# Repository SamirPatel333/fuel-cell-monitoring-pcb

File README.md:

# Fuel Cell Monitoring System – 6-Layer PCB

## Overview

A custom **6-layer mixed-signal PCB** designed in **KiCad** for monitoring a **PEM fuel cell system**.

The board measures fuel-cell voltage and current, conditions the analog signals, performs ADC conversion, provides digital isolation, and interfaces with an **ESP32-S3**.

## Main Features

- Fuel-cell voltage measurement
- Fuel-cell current measurement up to 20 A
- Analog signal conditioning and filtering
- Precision voltage references
- High-resolution ADC measurement
- Digital isolation
- ESP32-S3 interface

## Main Components

| Component | Function |
|---|---|
| ESP32-S3 | Microcontroller |
| ADS8329 | ADC |
| MAX49925 | Current measurement |
| MAX6070 | Precision voltage reference |
| AD8031 / AD8032 | Analog signal conditioning |
| ADA4099 | Precision analog amplifier |

## PCB Design

The PCB is designed as a **6-layer mixed-signal board** using KiCad.

The multilayer design supports:

- Analog and digital signal separation
- Stable power and ground distribution
- Sensitive ADC signal routing
- High-current routing
- Improved signal integrity and noise performance

## Design Tools

- KiCad – Schematic capture and PCB layout
- ESP32-S3 – Microcontroller interface
- Multilayer PCB design for mixed-signal applications

## Project Structure

- `Kicad/` – KiCad schematics, PCB layout, symbols and footprints
- `Docs/` – Project report and documentation images
- `.gitignore` – Files excluded from Git tracking

## Project Status

PCB schematic and 6-layer PCB layout completed in KiCad.

## Future Improvements

- PCB manufacturing and assembly
- Hardware testing and calibration
- ESP32-S3 firmware development
- Measurement accuracy and noise evaluation

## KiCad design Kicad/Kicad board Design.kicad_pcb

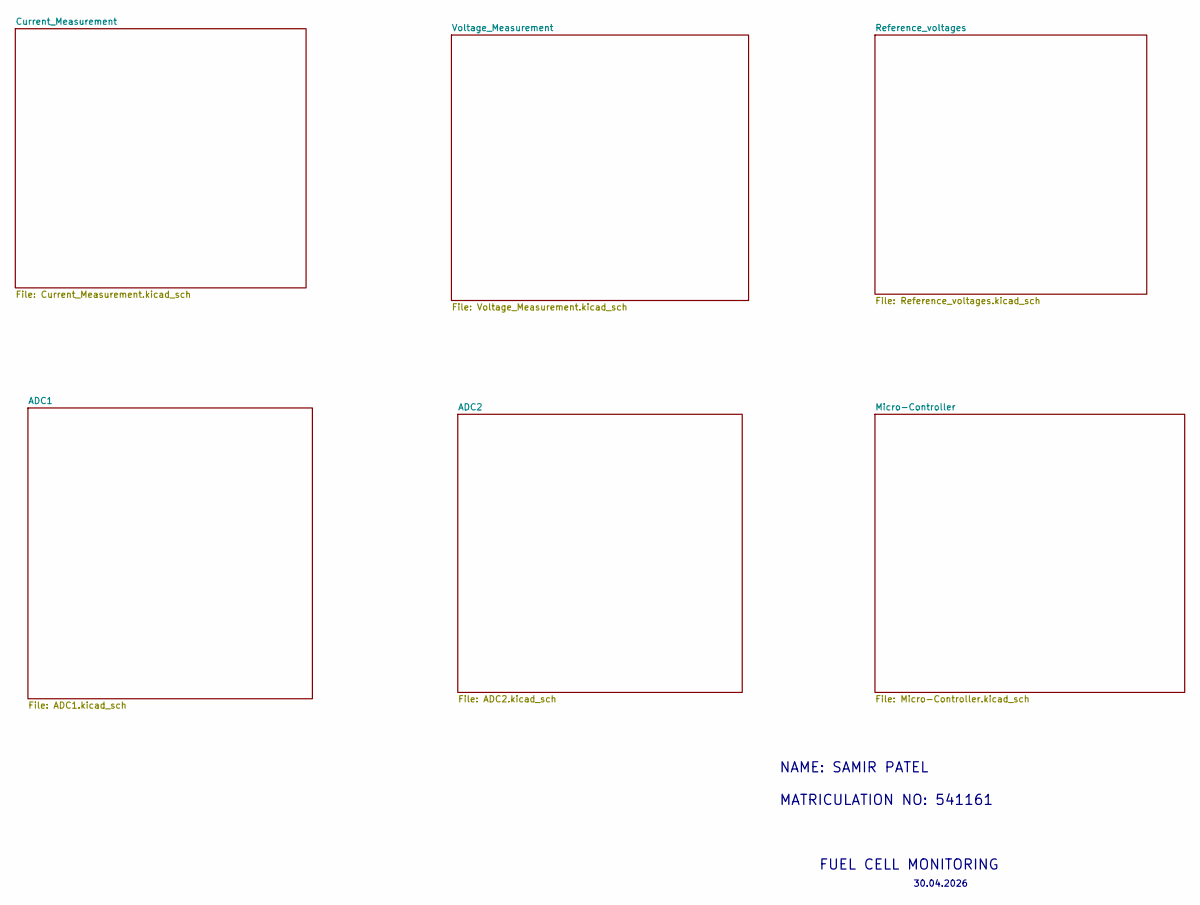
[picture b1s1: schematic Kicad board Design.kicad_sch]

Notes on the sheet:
FUEL CELL MONITORING
30.04.2026
NAME: SAMIR PATEL MATRICULATION NO: 541161

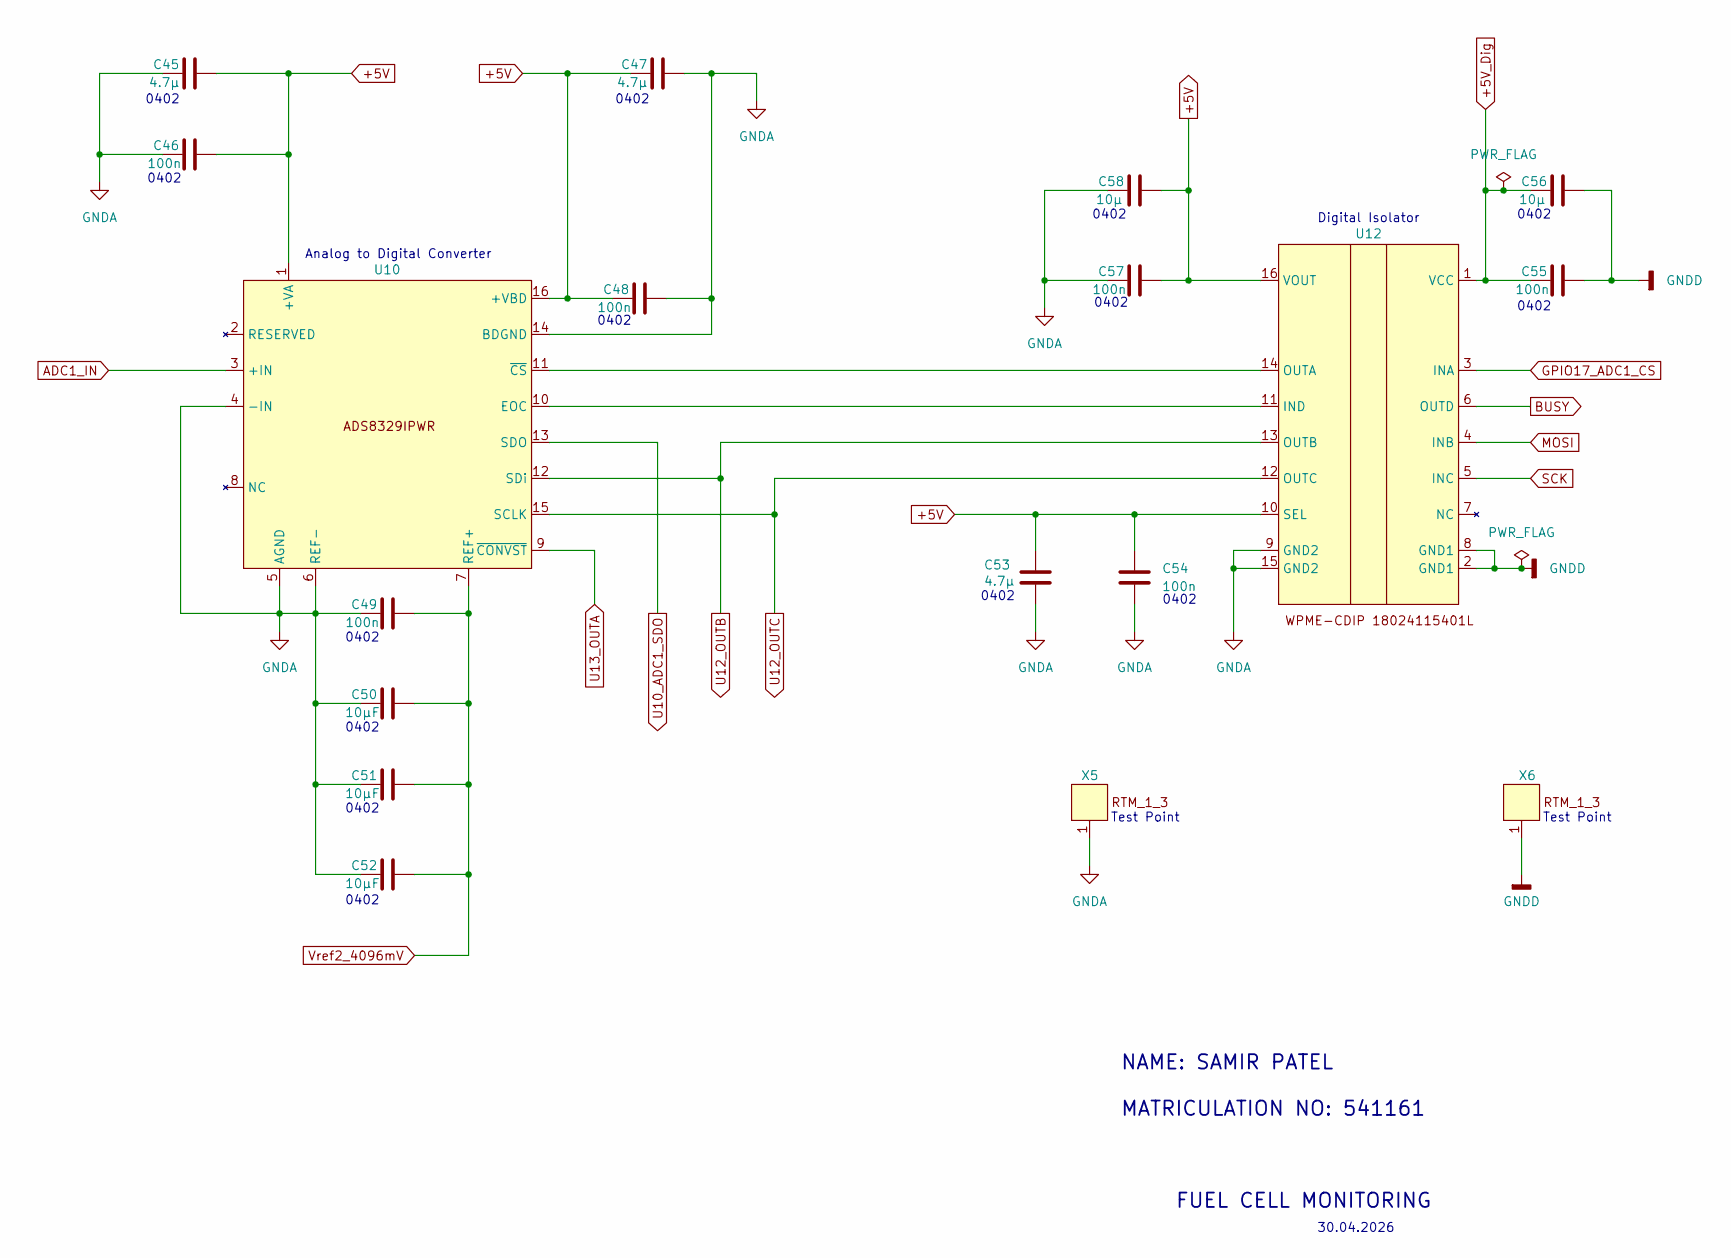
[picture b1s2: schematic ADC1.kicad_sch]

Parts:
C45, C47, C53: 4.7µ; C_0402_1005Metric
C46, C48, C49, C54, C55, C57: 100n; C_0402_1005Metric
C50, C51, C52: 10µF; C_0402_1005Metric
C56, C58: 10µ; C_0402_1005Metric
U10: ADS8329IPWR
U12: WPME-CDIP 18024115401L
X5, X6: RTM_1_3

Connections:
+5V: C45.2, C46.2, C47.1, C48.1, C53.1, C54.1, C57.2, C58.2, U10.1 (+VA), U10.16 (+VBD), U12.10 (SEL), U12.16 (VOUT); also elsewhere on the board
+5V_Dig: C55.1, C56.1, U12.1 (VCC); also elsewhere on the board
ADC1_IN: U10.3 (+IN); also elsewhere on the board
BUSY: U12.6 (OUTD); also elsewhere on the board
GNDA: C45.1, C46.1, C47.2, C48.2, C49.1, C50.1, C51.1, C52.1, C53.2, C54.2, C57.1, C58.1, U10.4 (-IN), U10.5 (AGND), U10.6 (REF-), U10.14 (BDGND), U12.9 (GND2), U12.15 (GND2), X5.1; also elsewhere on the board
GNDD: C55.2, C56.2, U12.2 (GND1), U12.8 (GND1), X6.1; also elsewhere on the board
GPIO17_ADC1_CS: U12.3 (INA); also elsewhere on the board
MOSI: U12.4 (INB); also elsewhere on the board
unnamed: U10.10 (EOC), U12.11 (IND)
unnamed: U10.11 (~CS), U12.14 (OUTA)
SCK: U12.5 (INC); also elsewhere on the board
U10_ADC1_SDO: U10.13 (SDO); also elsewhere on the board
U12_OUTB: U10.12 (SDi), U12.13 (OUTB); also elsewhere on the board
U12_OUTC: U10.15 (SCLK), U12.12 (OUTC); also elsewhere on the board
U13_OUTA: U10.9 (~CONVST); also elsewhere on the board
Vref2_4096mV: C49.2, C50.2, C51.2, C52.2, U10.7 (REF+); also elsewhere on the board

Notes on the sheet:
0402
Test Point
Analog to Digital Converter
NAME: SAMIR PATEL MATRICULATION NO: 541161
30.04.2026
Digital Isolator
FUEL CELL MONITORING

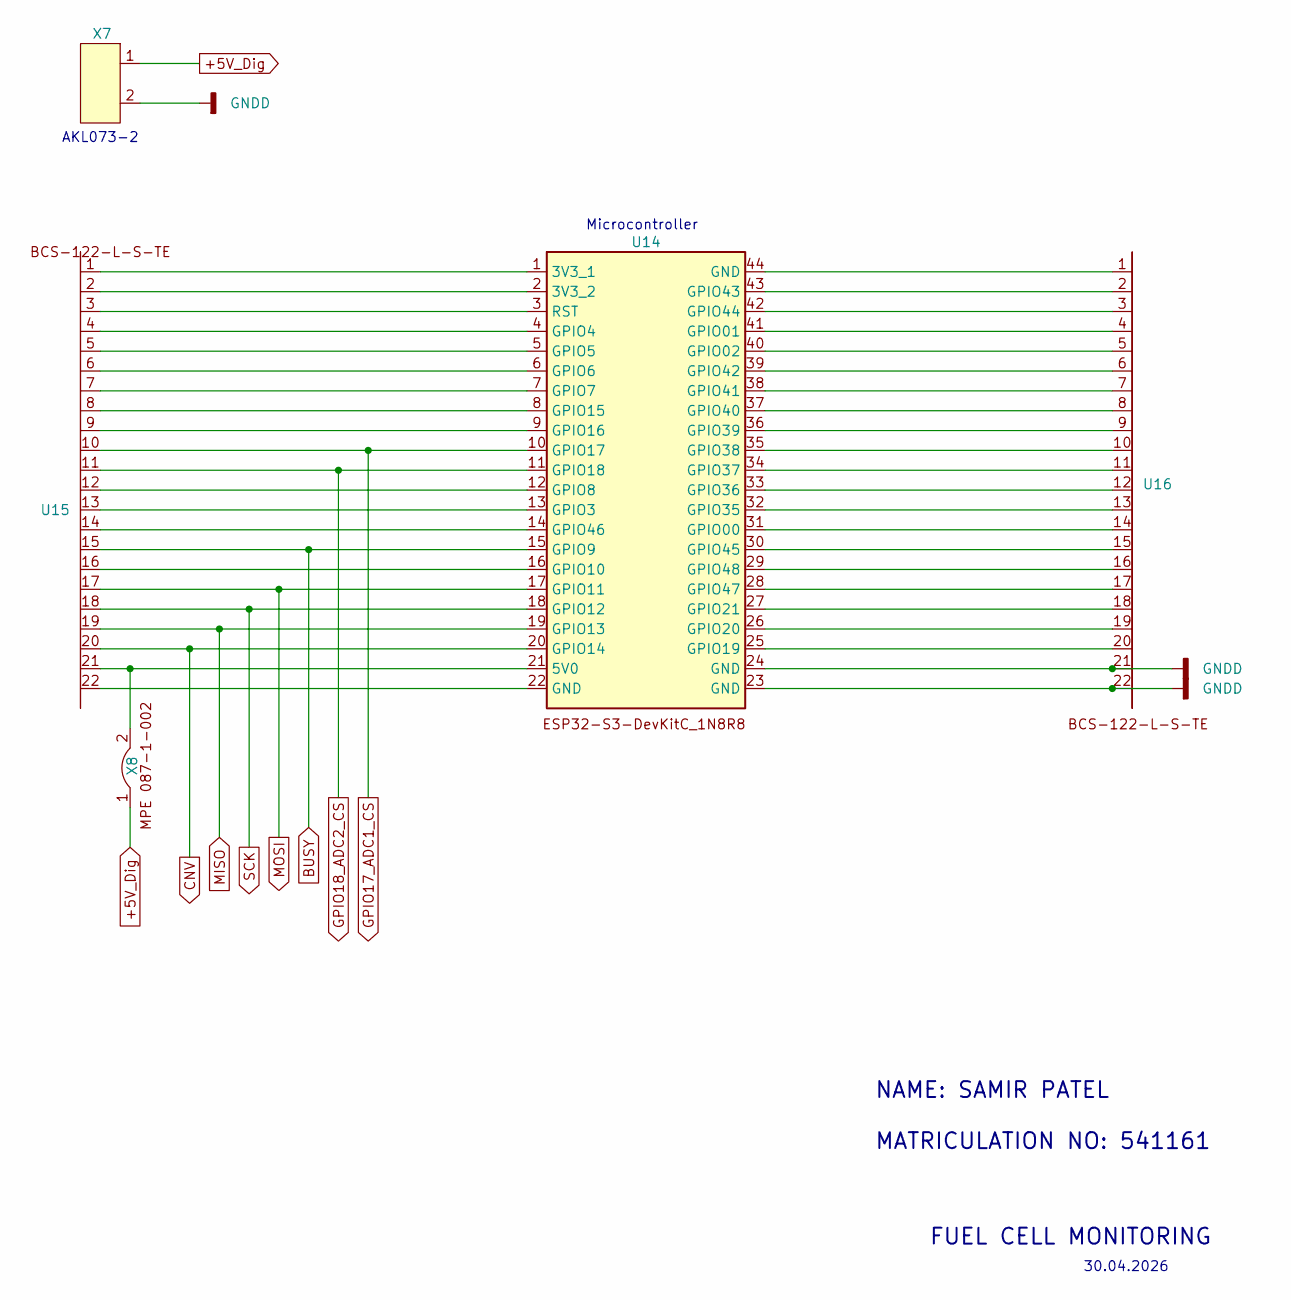
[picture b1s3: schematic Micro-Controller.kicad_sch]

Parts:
U14: ESP32-S3-DevkitC-1N8R8
U15, U16: BCS-122-L-S-TE
X7: AKL073-2
X8: MPE_087

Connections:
+5V_Dig: X7.1, X8.1; also elsewhere on the board
BUSY: U14.15 (GPIO9), U15.15; also elsewhere on the board
CNV: U14.20 (GPIO14), U15.20; also elsewhere on the board
GNDD: U14.23 (GND), U14.24 (GND), U16.21, U16.22, X7.2; also elsewhere on the board
GPIO17_ADC1_CS: U14.10 (GPIO17), U15.10; also elsewhere on the board
GPIO18_ADC2_CS: U14.11 (GPIO18), U15.11; also elsewhere on the board
MISO: U14.19 (GPIO13), U15.19; also elsewhere on the board
MOSI: U14.17 (GPIO11), U15.17; also elsewhere on the board
unnamed: U14.1 (3V3_1), U15.1
unnamed: U14.2 (3V3_2), U15.2
unnamed: U14.3 (RST), U15.3
unnamed: U14.4 (GPIO4), U15.4
unnamed: U14.5 (GPIO5), U15.5
unnamed: U14.6 (GPIO6), U15.6
unnamed: U14.7 (GPIO7), U15.7
unnamed: U14.8 (GPIO15), U15.8
unnamed: U14.9 (GPIO16), U15.9
unnamed: U14.12 (GPIO8), U15.12
unnamed: U14.13 (GPIO3), U15.13
unnamed: U14.14 (GPIO46), U15.14
unnamed: U14.16 (GPIO10), U15.16
unnamed: U14.21 (5V0), U15.21, X8.2
unnamed: U14.22 (GND), U15.22
unnamed: U14.44 (GND), U16.1
unnamed: U14.43 (GPIO43), U16.2
unnamed: U14.42 (GPIO44), U16.3
unnamed: U14.41 (GPIO01), U16.4
unnamed: U14.40 (GPIO02), U16.5
unnamed: U14.39 (GPIO42), U16.6
unnamed: U14.38 (GPIO41), U16.7
unnamed: U14.37 (GPIO40), U16.8
unnamed: U14.36 (GPIO39), U16.9
unnamed: U14.35 (GPIO38), U16.10
unnamed: U14.34 (GPIO37), U16.11
unnamed: U14.33 (GPIO36), U16.12
unnamed: U14.32 (GPIO35), U16.13
unnamed: U14.31 (GPIO00), U16.14
unnamed: U14.30 (GPIO45), U16.15
unnamed: U14.29 (GPIO48), U16.16
unnamed: U14.28 (GPIO47), U16.17
unnamed: U14.27 (GPIO21), U16.18
unnamed: U14.26 (GPIO20), U16.19
unnamed: U14.25 (GPIO19), U16.20
SCK: U14.18 (GPIO12), U15.18; also elsewhere on the board

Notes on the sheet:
30.04.2026
Microcontroller
NAME: SAMIR PATEL MATRICULATION NO: 541161
FUEL CELL MONITORING
AKL073-2

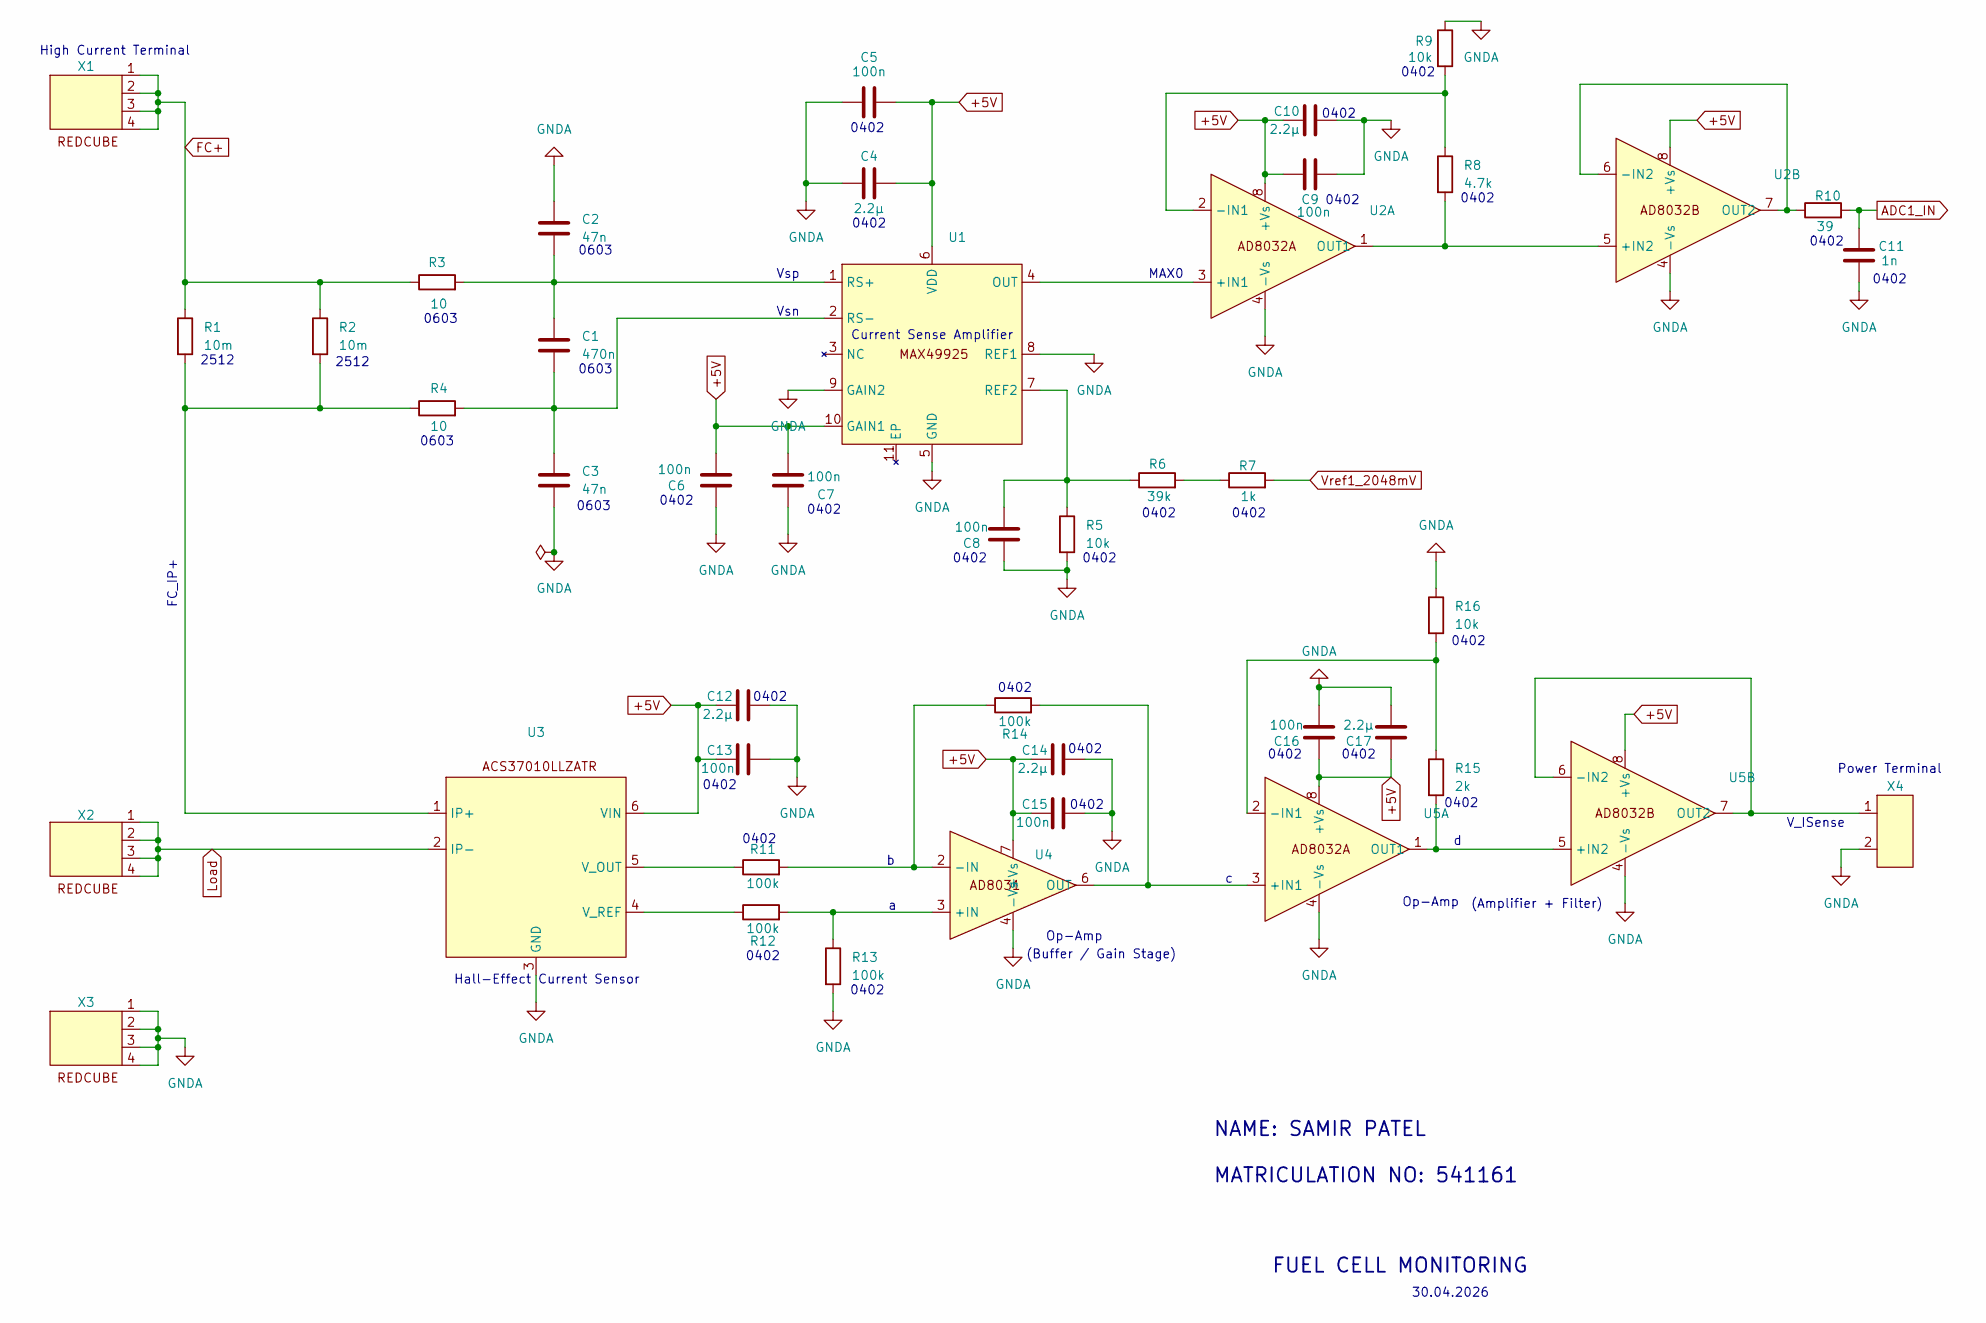
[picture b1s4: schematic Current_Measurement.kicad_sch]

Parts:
C1: 470n; C_0603_1608Metric
C2, C3: 47n; C_0603_1608Metric
C4, C10, C12, C14, C17: 2.2µ; C_0402_1005Metric
C5, C6, C7, C8, C9, C13, C15, C16: 100n; C_0402_1005Metric
C11: 1n; C_0402_1005Metric
R1, R2: 10m; R_2512_6332Metric
R3, R4: 10; R_0603_1608Metric
R5, R9, R16: 10k; R_0402_1005Metric
R6: 39k; R_0402_1005Metric
R7: 1k; R_0402_1005Metric
R8: 4.7k; R_0402_1005Metric
R10: 39; R_0402_1005Metric
R11, R12, R13, R14: 100k; R_0402_1005Metric
R15: 2k; R_0402_1005Metric
U1: MAX49925XATB+T
U2, U5: AD8032ARZ
U3: ACS37010LLZATR-030U5
U4: AD8031ARZ
X1, X2, X3: WP-THRBU_REDCUBE_74650073
X4: AKL073-2

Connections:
+5V: C4.2, C5.2, C6.1, C7.1, C9.1, C10.1, C12.1, C13.1, C14.1, C15.1, C16.2, C17.2, U1.6 (VDD), U1.10 (GAIN1), U2.8 (+Vs), U3.6 (VIN), U4.7 (+Vs), U5.8 (+Vs); also elsewhere on the board
ADC1_IN: C11.1, R10.2; also elsewhere on the board
FC+: R1.1, R2.1, R3.1, X1.1, X1.2, X1.3, X1.4; also elsewhere on the board
GNDA: C2.1, C3.2, C4.1, C5.1, C6.2, C7.2, C8.2, C9.2, C10.2, C11.2, C12.2, C13.2, C14.2, C15.2, C16.1, C17.1, R5.2, R9.1, R13.2, R16.1, U1.5 (GND), U1.8 (REF1), U1.9 (GAIN2), U2.4 (-Vs), U3.3 (GND), U4.4 (-Vs), U5.4 (-Vs), X3.1, X3.2, X3.3, X3.4, X4.2; also elsewhere on the board
Load: U3.2 (IP-), X2.1, X2.2, X2.3, X2.4
unnamed: R6.2, R7.1
unnamed: U1.4 (OUT), U2.3 (+IN1)
unnamed: C8.1, R5.1, R6.1, U1.7 (REF2)
unnamed: C1.1, C2.2, R3.2, U1.1 (RS+)
unnamed: C1.2, C3.1, R4.2, U1.2 (RS-)
unnamed: R8.1, R9.2, U2.2 (-IN1)
unnamed: R8.2, U2.1 (OUT1), U2.5 (+IN2)
unnamed: R10.1, U2.6 (-IN2), U2.7 (OUT2)
unnamed: R1.2, R2.2, R4.1, U3.1 (IP+)
unnamed: R11.1, U3.5 (V_OUT)
unnamed: R12.1, U3.4 (V_REF)
unnamed: R12.2, R13.1, U4.3 (+IN)
unnamed: R11.2, R14.1, U4.2 (-IN)
unnamed: R14.2, U4.6 (OUT), U5.3 (+IN1)
unnamed: R15.1, R16.2, U5.2 (-IN1)
unnamed: R15.2, U5.1 (OUT1), U5.5 (+IN2)
unnamed: U5.6 (-IN2), U5.7 (OUT2), X4.1
Vref1_2048mV: R7.2; also elsewhere on the board

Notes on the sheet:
Hall-Effect Current Sensor
0402
2512
0603
V_ISense
FUEL CELL MONITORING
Vsp
Current Sense Amplifier
NAME: SAMIR PATEL MATRICULATION NO: 541161
High Current Terminal
Vsn
30.04.2026
(Buffer / Gain Stage)
FC_IP+
Op-Amp
MAX0
(Amplifier + Filter)
Power Terminal

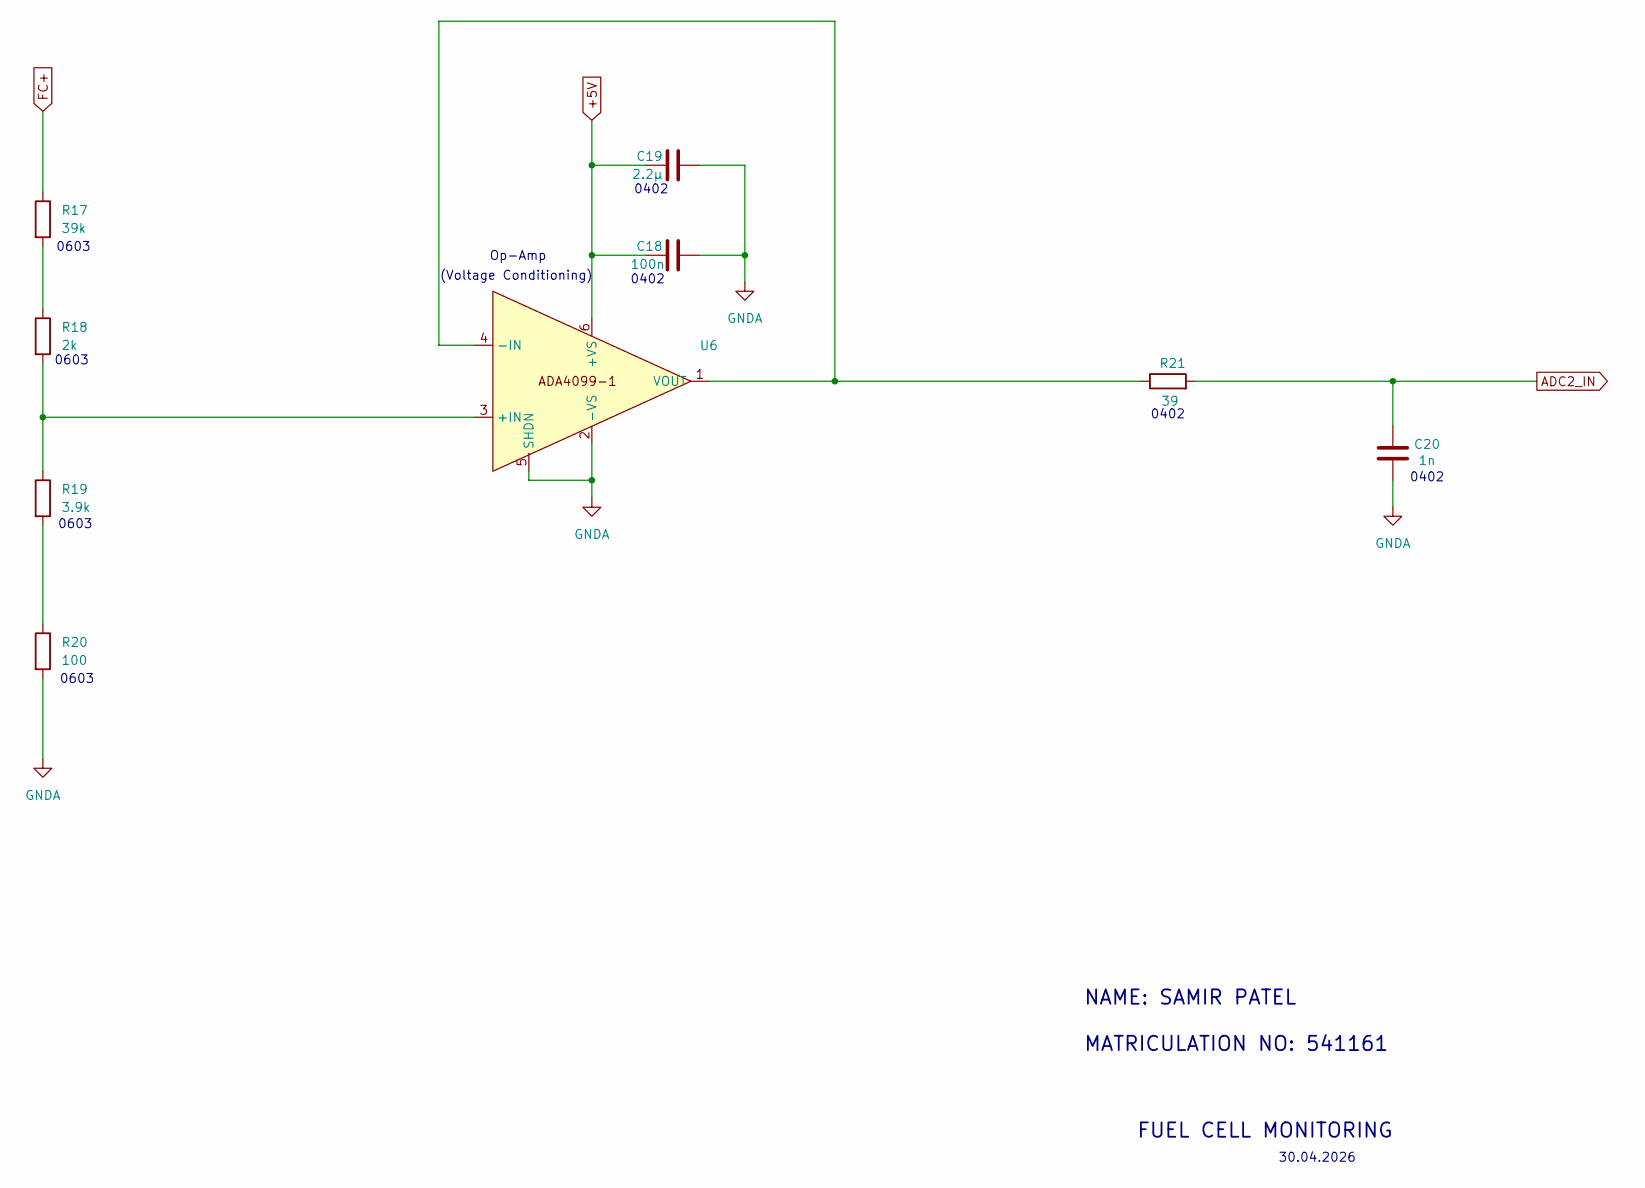
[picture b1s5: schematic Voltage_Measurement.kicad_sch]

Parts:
C18: 100n; C_0402_1005Metric
C19: 2.2µ; C_0402_1005Metric
C20: 1n; C_0402_1005Metric
R17: 39k; R_0603_1608Metric
R18: 2k; R_0603_1608Metric
R19: 3.9k; R_0603_1608Metric
R20: 100; R_0603_1608Metric
R21: 39; R_0402_1005Metric
U6: ADA4099-1BUJZ-RL7

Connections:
+5V: C18.1, C19.1, U6.6 (+VS); also elsewhere on the board
ADC2_IN: C20.1, R21.2; also elsewhere on the board
FC+: R17.1; also elsewhere on the board
GNDA: C18.2, C19.2, C20.2, R20.2, U6.2 (-VS), U6.5 (SHDN); also elsewhere on the board
unnamed: R17.2, R18.1
unnamed: R19.2, R20.1
unnamed: R18.2, R19.1, U6.3 (+IN)
unnamed: R21.1, U6.1 (VOUT), U6.4 (-IN)

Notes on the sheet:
0402
0603
(Voltage Conditioning)
FUEL CELL MONITORING
Op-Amp
NAME: SAMIR PATEL MATRICULATION NO: 541161
30.04.2026

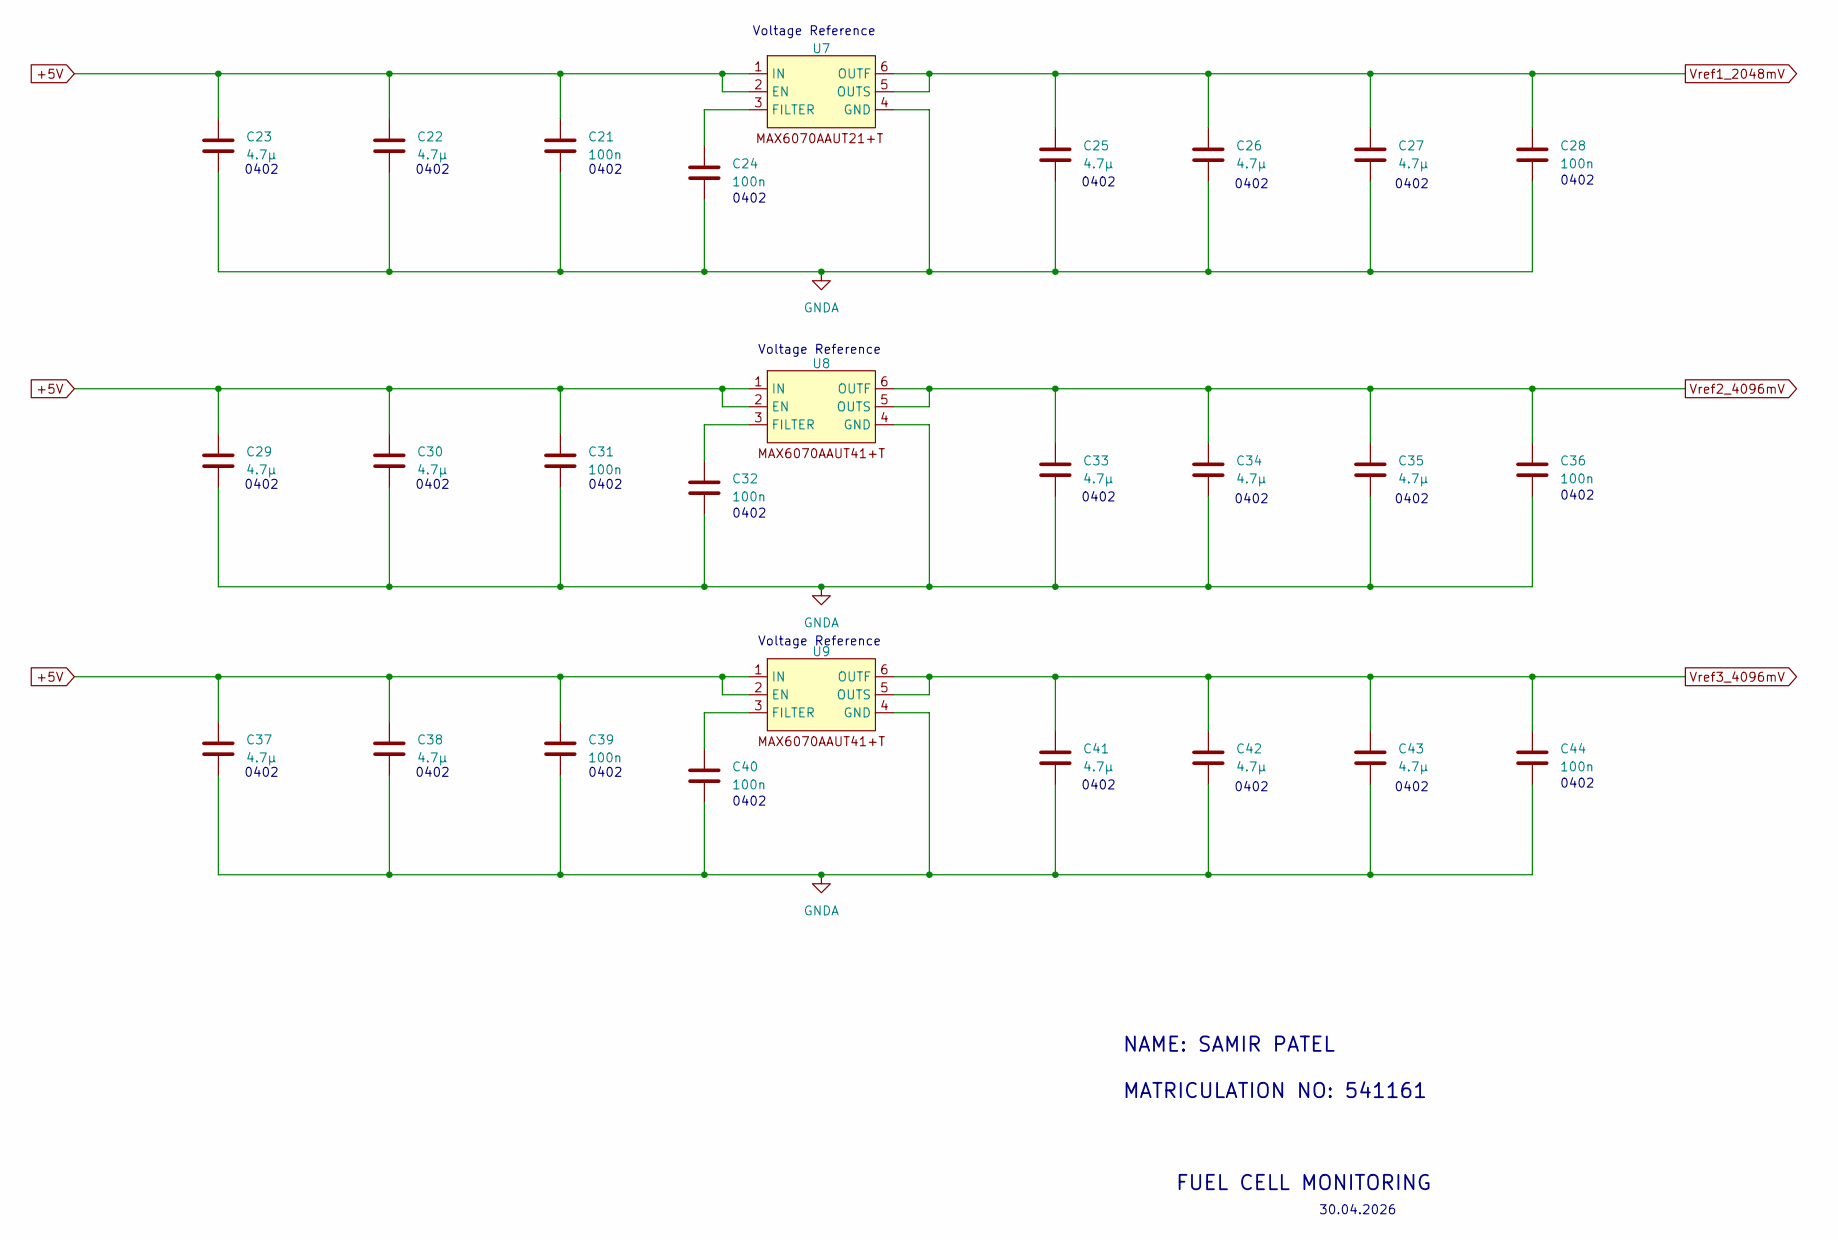
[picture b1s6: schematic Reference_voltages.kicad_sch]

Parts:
C21, C24, C28, C31, C32, C36, C39, C40, C44: 100n; C_0402_1005Metric
C22, C23, C25, C26, C27, C29, C30, C33, C34, C35, C37, C38, C41, C42, C43: 4.7µ; C_0402_1005Metric
U7: MAX6070AAUT21+T
U8, U9: MAX6070AAUT41+T

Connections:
+5V: C21.1, C22.1, C23.1, C29.1, C30.1, C31.1, C37.1, C38.1, C39.1, U7.1 (IN), U7.2 (EN), U8.1 (IN), U8.2 (EN), U9.1 (IN), U9.2 (EN); also elsewhere on the board
GNDA: C21.2, C22.2, C23.2, C24.2, C25.2, C26.2, C27.2, C28.2, C29.2, C30.2, C31.2, C32.2, C33.2, C34.2, C35.2, C36.2, C37.2, C38.2, C39.2, C40.2, C41.2, C42.2, C43.2, C44.2, U7.4 (GND), U8.4 (GND), U9.4 (GND); also elsewhere on the board
unnamed: C24.1, U7.3 (FILTER)
unnamed: C32.1, U8.3 (FILTER)
unnamed: C40.1, U9.3 (FILTER)
Vref1_2048mV: C25.1, C26.1, C27.1, C28.1, U7.5 (OUTS), U7.6 (OUTF); also elsewhere on the board
Vref2_4096mV: C33.1, C34.1, C35.1, C36.1, U8.5 (OUTS), U8.6 (OUTF); also elsewhere on the board
Vref3_4096mV: C41.1, C42.1, C43.1, C44.1, U9.5 (OUTS), U9.6 (OUTF); also elsewhere on the board

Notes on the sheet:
Voltage Reference
0402
30.04.2026
FUEL CELL MONITORING
NAME: SAMIR PATEL MATRICULATION NO: 541161

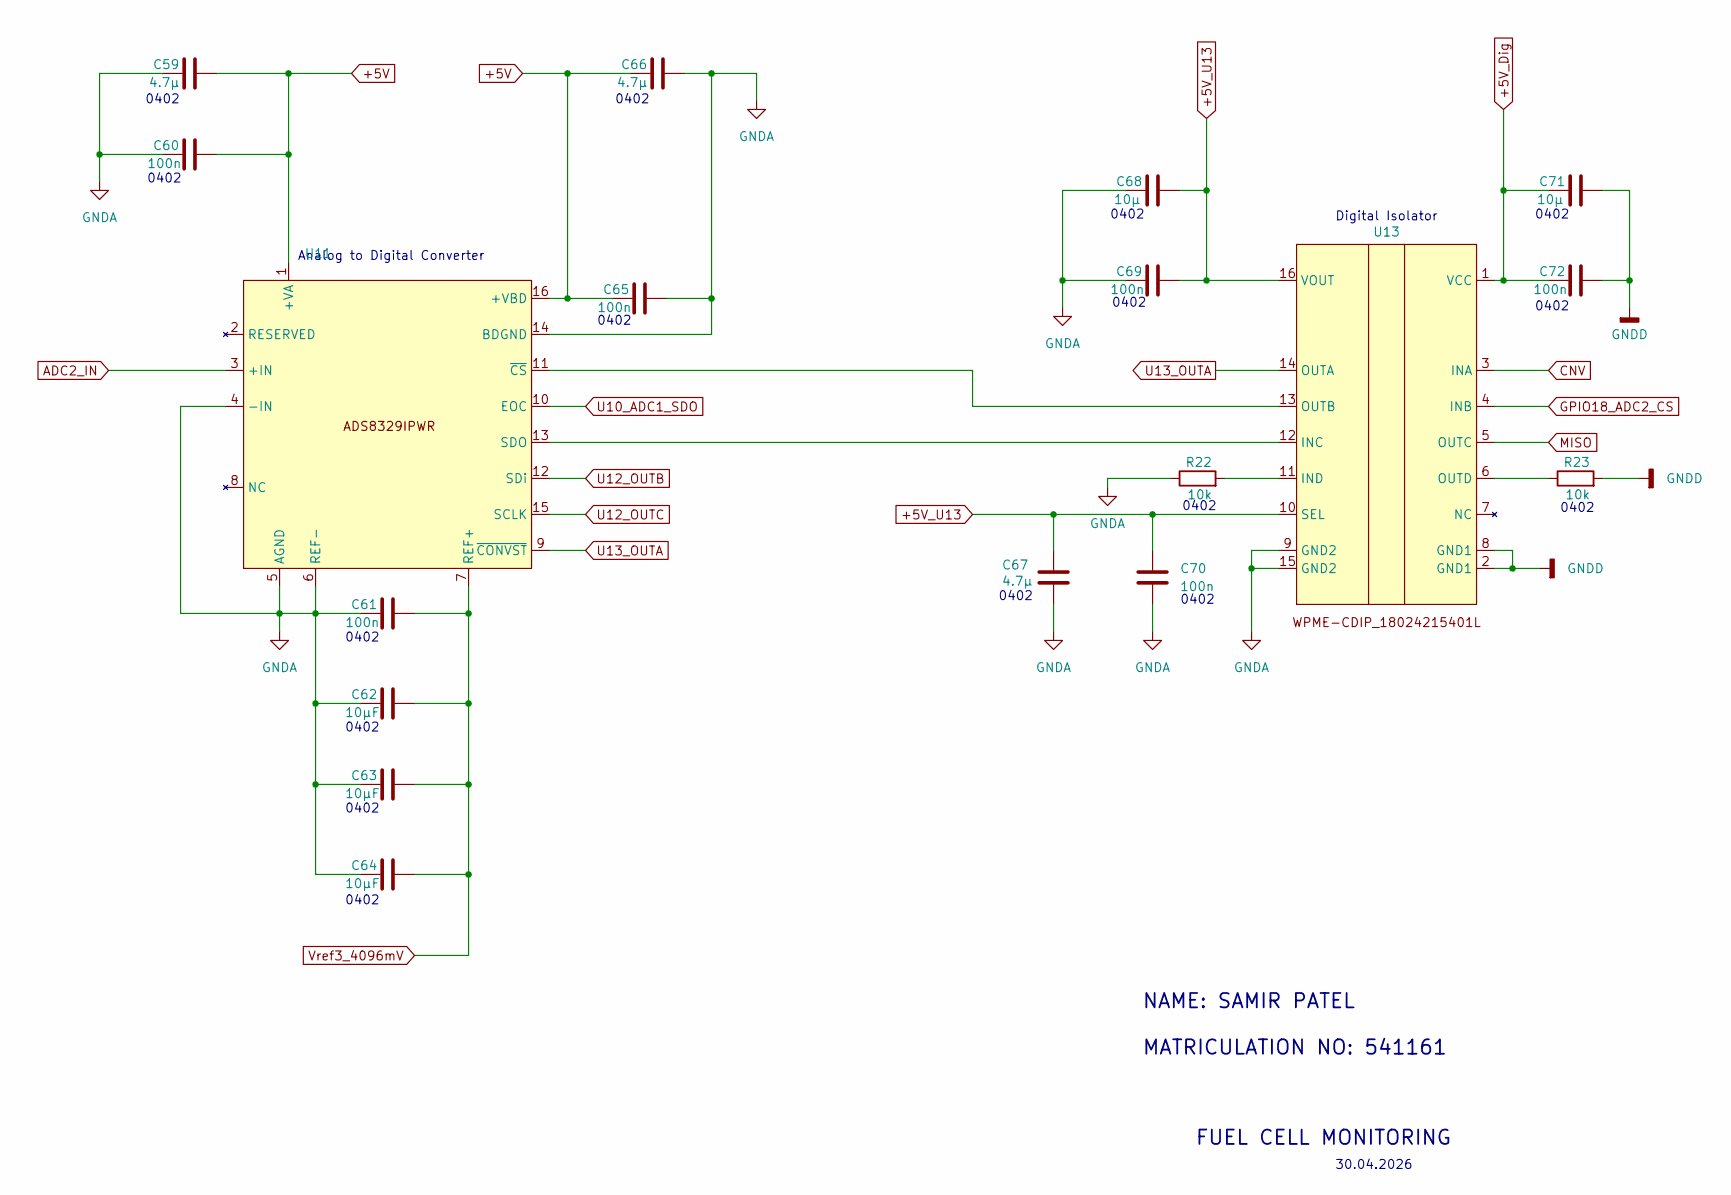
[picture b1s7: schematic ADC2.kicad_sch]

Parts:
C59, C66, C67: 4.7µ; C_0402_1005Metric
C60, C61, C65, C69, C70, C72: 100n; C_0402_1005Metric
C62, C63, C64: 10µF; C_0402_1005Metric
C68, C71: 10µ; C_0402_1005Metric
R22, R23: 10k; R_0402_1005Metric
U11: ADS8329IPWR
U13: WPME-CDIP 18024215401L

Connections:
+5V: C59.2, C60.2, C65.1, C66.1, U11.1 (+VA), U11.16 (+VBD); also elsewhere on the board
+5V_Dig: C71.1, C72.1, U13.1 (VCC); also elsewhere on the board
+5V_U13: C67.1, C68.2, C69.2, C70.1, U13.10 (SEL), U13.16 (VOUT)
ADC2_IN: U11.3 (+IN); also elsewhere on the board
CNV: U13.3 (INA); also elsewhere on the board
GNDA: C59.1, C60.1, C61.1, C62.1, C63.1, C64.1, C65.2, C66.2, C67.2, C68.1, C69.1, C70.2, R22.1, U11.4 (-IN), U11.5 (AGND), U11.6 (REF-), U11.14 (BDGND), U13.9 (GND2), U13.15 (GND2); also elsewhere on the board
GNDD: C71.2, C72.2, R23.2, U13.2 (GND1), U13.8 (GND1); also elsewhere on the board
GPIO18_ADC2_CS: U13.4 (INB); also elsewhere on the board
MISO: U13.5 (OUTC); also elsewhere on the board
unnamed: U11.13 (SDO), U13.12 (INC)
unnamed: U11.11 (~CS), U13.13 (OUTB)
unnamed: R22.2, U13.11 (IND)
unnamed: R23.1, U13.6 (OUTD)
U10_ADC1_SDO: U11.10 (EOC); also elsewhere on the board
U12_OUTB: U11.12 (SDi); also elsewhere on the board
U12_OUTC: U11.15 (SCLK); also elsewhere on the board
U13_OUTA: U11.9 (~CONVST), U13.14 (OUTA); also elsewhere on the board
Vref3_4096mV: C61.2, C62.2, C63.2, C64.2, U11.7 (REF+); also elsewhere on the board

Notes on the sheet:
Analog to Digital Converter
30.04.2026
Digital Isolator
0402
NAME: SAMIR PATEL MATRICULATION NO: 541161
FUEL CELL MONITORING

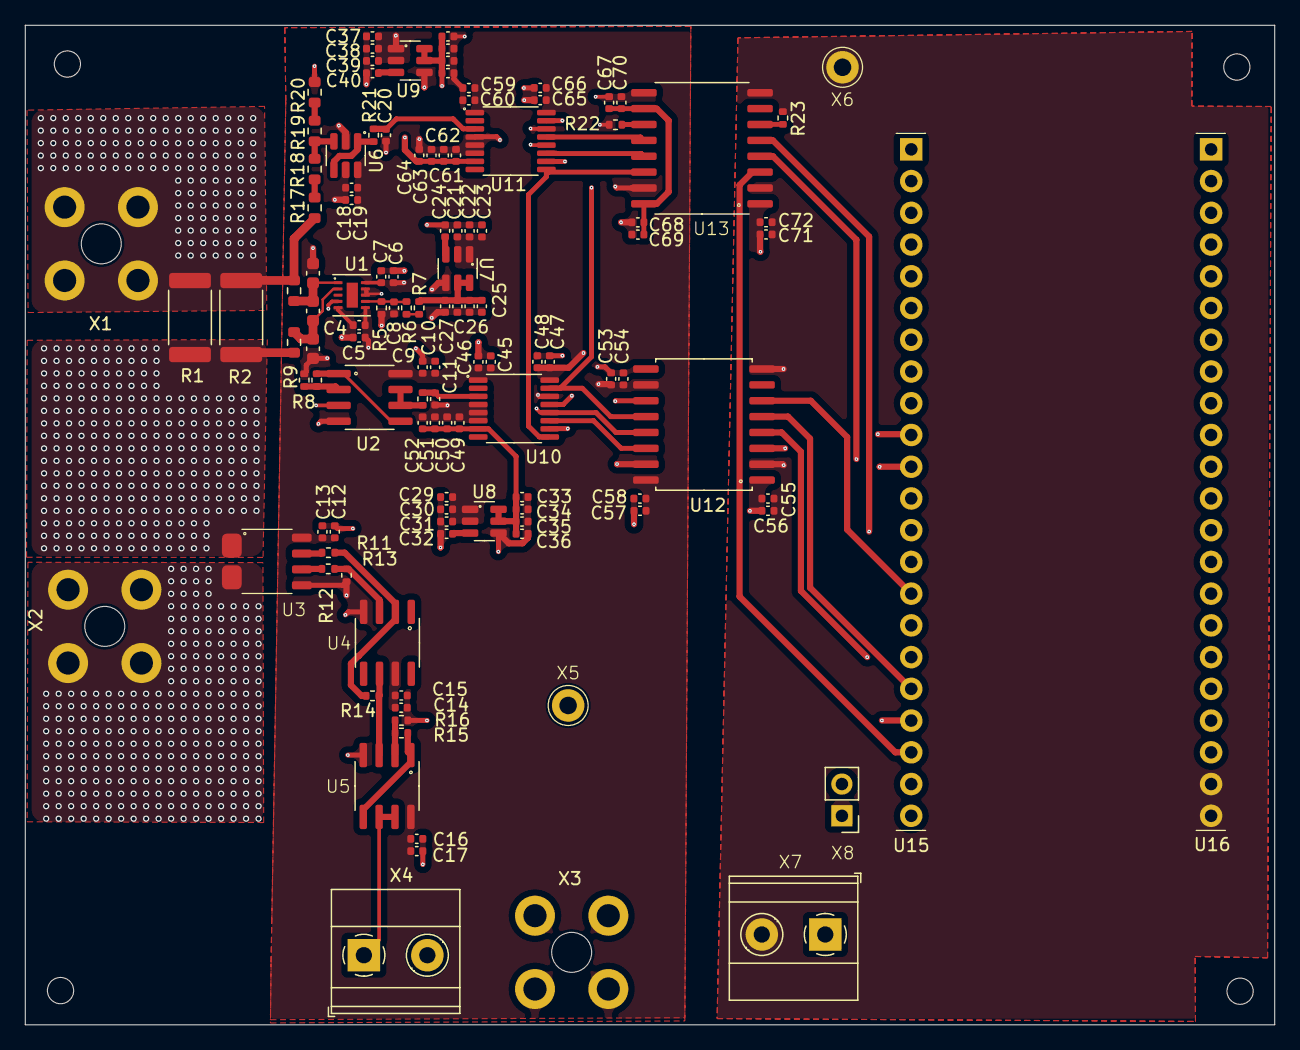
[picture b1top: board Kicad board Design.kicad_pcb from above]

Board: 6 copper layers, 100.0 x 80.0 mm, 118 parts (0 on the bottom side), 54 nets.
